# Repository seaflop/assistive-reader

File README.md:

# Embedded OCR-to-Speech System for Visually Impaired Users

## About
This repository contains the code for a wearable device that helps visually impaired users to read text in natural scene conditions. There is also a version of the script that can be run on Windows/POSIX-compliant machines to test functionality. Both versions are capable of taking a picture, performing optical character recognition on it, and producing a text-to-speech output for the user.

This script uses [RapidOCR](https://github.com/RapidAI/RapidOCR) for text detection/recognition and [Piper](https://github.com/rhasspy/piper) for text-to-speech functionality (thank you Danny!).

This project is still in progress, so check back every once in a while for updates!

Expected completion: April 2026

## Setup for POSIX/Windows

*Ensure that you have Python version 3.10.0 or later installed on your system.*

```
python --version
```

**NOTE:** *Since this project uses the pynput package for monitoring keyboard events, this script will not work on Linux DEs using the Wayland Protocol and requires sudo permissions to work on MacOS.*

**1. Download/Clone the repository in any directory you'd like.**

```
git clone https://github.com/seaflop/capstone/tree/testing
```

**2. Navigate to the `capstone` directory.**

```
cd capstone
```

**3. Activate a Python virtual environment.**

POSIX:

```
python3 -m venv .venv
source .venv/bin/activate
```

Windows:

```
python -m venv .venv
.venv\Scripts\Activate
```

**4. Download the required packages.**

```
pip insatll --upgrade pip
pip install -r requirements.txt
```

**5. Run the Script**

Run the script from the `capstone` directory.

Flags:  
`-w`: Use the webcam to take a picture.  
`-i`: Specify the path to an existing image.  
*Use of at least one of these flags is required*

POSIX:

```
python ./src/main.py -i "pathtoyourimagehere.jpg"
python ./src/main.py -w
```

Windows:

```
python .\src\main.py -i "pathtoyourimagehere.jpg"
python .\src\main.py -w
```

The script will prompt you for input when it is ready to run. This may take some time, especially on the first run, as all the models will have to be downloaded first.

Press Space to start the script.  
If you specified `-w`, press Space to take a picture, or Esc to exit.  
You can exit the script at any time by pressing the Esc key.  
Audio playback can be paused/resumed by pressing Space.

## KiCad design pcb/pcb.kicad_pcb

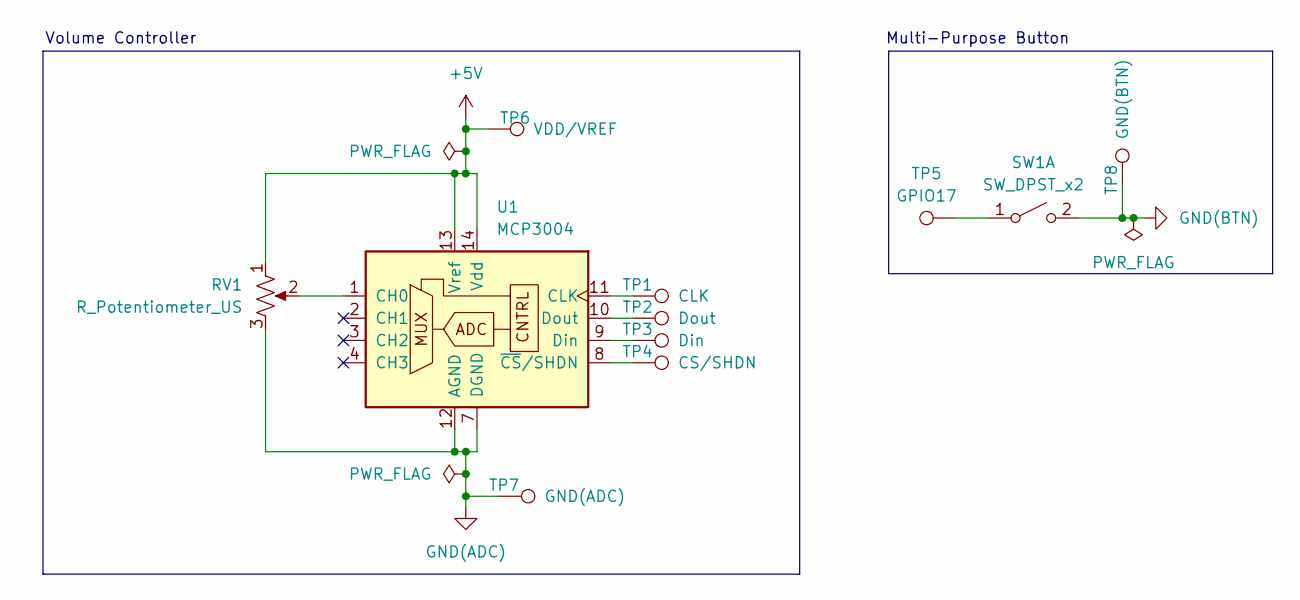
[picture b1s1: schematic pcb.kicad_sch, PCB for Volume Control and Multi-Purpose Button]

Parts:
RV1: R_Potentiometer_US; Potentiometer_Bourns_3314J_Vertical; LCSC C36376
SW1: SW_DPST_x2; SW_Push_1TS009xxxx-xxxx-xxxx_6x6x5mm; LCSC C97448
TP1: CLK; TestPoint_Pad_D2.5mm
TP2: Dout; TestPoint_Pad_D2.5mm
TP3: Din; TestPoint_Pad_D2.5mm
TP4: CS/SHDN; TestPoint_Pad_D2.5mm
TP5: GPIO17; TestPoint_Pad_D2.5mm
TP6: VDD/VREF; TestPoint_Pad_D2.5mm
TP7: GND(ADC); TestPoint_Pad_D2.5mm
TP8: GND(BTN); TestPoint_Pad_D2.5mm
U1: MCP3004; TSSOP-14_4.4x5mm_P0.65mm; LCSC C637056

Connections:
+5V: RV1.1, TP6.1, U1.13 (Vref), U1.14 (Vdd)
GND(ADC): RV1.3, TP7.1, U1.7 (DGND), U1.12 (AGND)
GND(BTN): SW1.2 (B), TP8.1
unnamed: SW1.1 (A), TP5.1
unnamed: RV1.2, U1.1 (CH0)
unnamed: TP1.1, U1.11 (CLK)
unnamed: TP3.1, U1.9 (Din)
unnamed: TP2.1, U1.10 (Dout)
unnamed: TP4.1, U1.8 (~CS/SHDN)

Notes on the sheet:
Multi-Purpose Button
Volume Controller

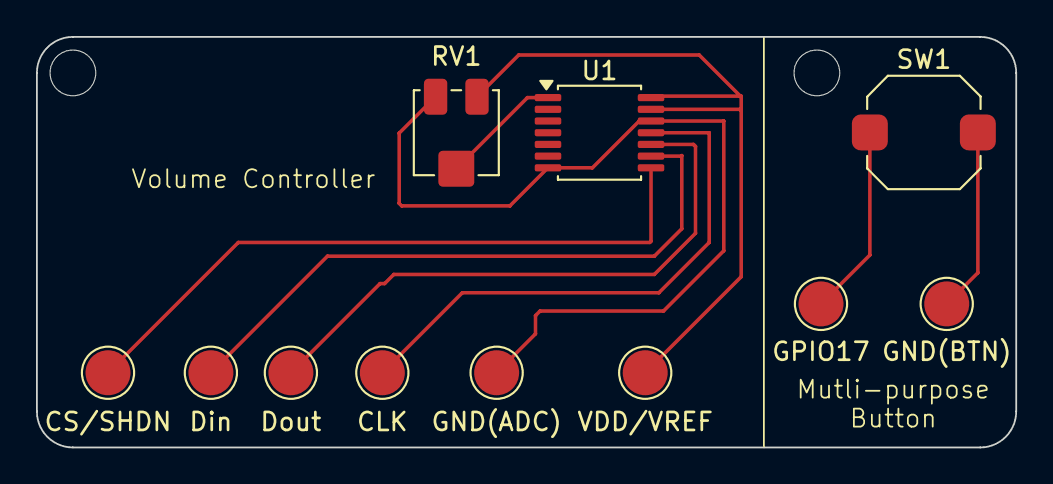
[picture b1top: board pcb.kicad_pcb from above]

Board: 2 copper layers, 54.4 x 22.8 mm, 11 parts (0 on the bottom side), 9 nets.

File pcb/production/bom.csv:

Designator,Footprint,Quantity,Value,LCSC Part #
RV1,Potentiometer_Bourns_3314J_Vertical,1,R_Potentiometer_US,C36376
SW1,SW_Push_1TS009xxxx-xxxx-xxxx_6x6x5mm,1,SW_DPST_x2,C97448
TP1,TestPoint_Pad_D2.5mm,1,CLK,
TP2,TestPoint_Pad_D2.5mm,1,Dout,
TP3,TestPoint_Pad_D2.5mm,1,Din,
TP4,TestPoint_Pad_D2.5mm,1,CS/SHDN,
TP5,TestPoint_Pad_D2.5mm,1,GPIO17,
TP6,TestPoint_Pad_D2.5mm,1,VDD/VREF,
TP7,TestPoint_Pad_D2.5mm,1,GND(ADC),
TP8,TestPoint_Pad_D2.5mm,1,GND(BTN),
U1,TSSOP-14_4.4x5mm_P0.65mm,1,MCP3004,C637056

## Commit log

2025-12-20 Created readme
2025-12-23 Added "press space to start script" functionality
    Rewrote some parts of main.py such that the script waits for the user to
    press the spacebar to execute.
2025-12-23 Added headings to README
2026-01-10 Refactored all the code. And I mean all of it.
    Changes:
    - Every functional part of the project is now written as an object.
    - Text-to-speech now uses piper-tts and the voice model used has been
    included
    - Wrote a more robust main script, capable of pausing/playing audio
    output as well as escaping from the script at any time by pressing the
2026-01-10 Updated .gitignore
2026-01-10 Updated README.md with setup instructions for Linux
2026-01-10 Removed __pycache__ from repo
2026-01-10 Fixed argument for image in main.py
    Fixed a bug in main.py that didn't take into account the argument for
    the image path and instead defaulted to the predefined path.
2026-01-10 Refer to previous commit, forgot to add this file
2026-01-13 Removed file_management.py
    Shi was unnecessary.
2026-01-13 Added webcam functionality
    Added a function in the Capstone class that opens the webcam and allows
    the user to take a picture.
2026-01-13 Updated function parameters to match
2026-01-13 It's proper now trust
    Updated main.py to be able to either use a predefined image location or
    take a picture with the webcam to perform ocr on.
2026-01-13 Removed unnecessary testing and comments
2026-01-13 Made it obvious when ocr is working
2026-01-13 Oopsie made a typo
2026-01-13 Added a main script for Raspberry Pi deployment.
2026-01-13 Modified rpi-main.py to remove functionality that isn't compatible with the Pi
2026-01-20 added raspberry pi camera initialization and capture to file functionality
2026-01-20 Removed a blank line
2026-01-20 Added functionality.
    Button press now takes a picture if the script hasn't started yet.
    Removed some blank lines.
    Fixed an unintended behaviour where if there is no text is
    detected, the script would restart before the no text detected sound
    finished playing. This caused an error if the user tried to restart the
    script before the sound finished playing.
2026-03-17 Create PCB schematic and model for peripheral devices.
